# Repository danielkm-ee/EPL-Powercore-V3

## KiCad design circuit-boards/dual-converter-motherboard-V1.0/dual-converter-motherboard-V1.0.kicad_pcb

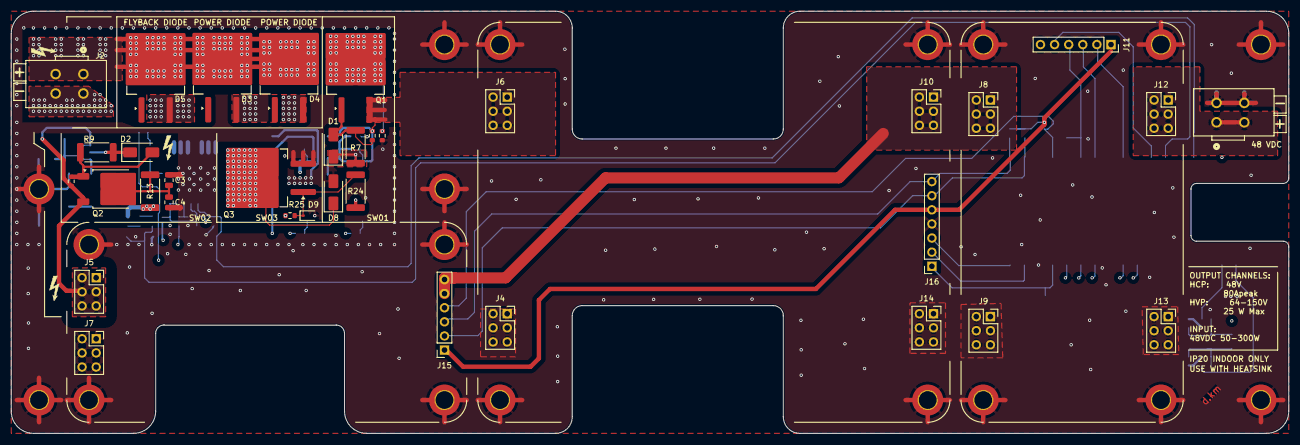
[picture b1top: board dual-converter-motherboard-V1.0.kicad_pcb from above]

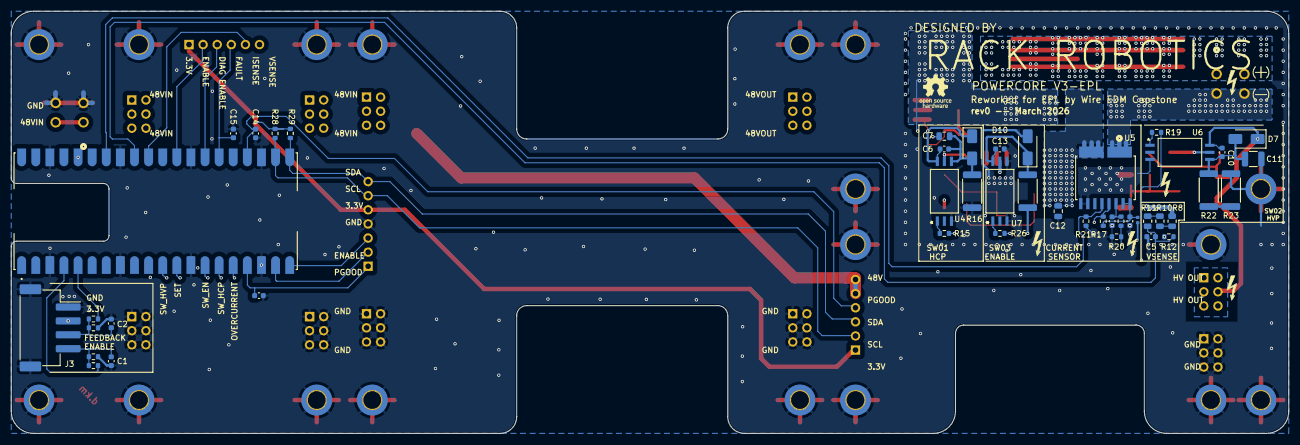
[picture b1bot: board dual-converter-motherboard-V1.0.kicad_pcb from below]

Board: 6 copper layers, 230.0 x 76.0 mm, 98 parts (45 on the bottom side), 49 nets.

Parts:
C1, C6, C8, C9, C10, C13: 220 nF; C_0603_1608Metric
C2, C14, C15, C16: 10000 pF; C_0603_1608Metric
C3, C4, C12: 10 nF; C_0805_2012Metric
C5: pF; C_0603_1608Metric
C7: 0.47 uF; C_0805_2012Metric
C11: 0.1 uF; C_1210_3225Metric
D1, D2, D8: US1M-13-F; D_SMA
D3, D4, D5: STPSC20065GY-TR
D6, D7, D10: D_Zener; D_SMA
D9: D_Zener; D_SOD-323
H1, H2, H3, H4, H5, H6, H7, H8, H9, H10, H11, H12, H13, H14, H15, H16, H17, H18: M3_DIN; MountingHole_3.2mm_M3_DIN965_Pad_TopBottom
J1, J2: 2601-1102
J3: S4B-XH-SM4-TB
J4, J5, J6, J7, J8, J9, J10, J12, J13, J14: Conn_02x03_Odd_Even; PinSocket_2x03_P2.54mm_Vertical
J11, J15: Conn_01x06_Socket; PinSocket_1x06_P2.54mm_Vertical
J16: Conn_01x07_Socket; PinSocket_1x07_P2.54mm_Vertical
L1: BBUP00100505330Y00; L_0402_1005Metric
Q1: SUM110P08-11L-E3
Q2: DMP45H4D9HK3-13
Q3: SIHB068N60EF-GE3; TO-263-2
R1, R2: 1K; R_0603_1608Metric
R3, R4, R12, R14, R17, R20, R21, R25: 10K; R_0603_1608Metric
R5, R6: 255K; R_0603_1608Metric
R7, R9, R24: 10R; R_2512_6332Metric
R8, R10, R11: 332K; R_0805_2012Metric
R13: 1R; R_2512_6332Metric
R15, R19, R26: 100R; R_0603_1608Metric
R16, R27: 1K; R_2512_6332Metric
R18, R28, R29: 2.2K; R_0603_1608Metric
R22, R23: 12K; R_2512_6332Metric
U4, U6, U7: UCC23313BDWYR
U5: TMCS1133C1A; TMCS1133C3AQDVGR
U8: SC0915

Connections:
+3.3V: J3.2, J11.1, J15.1, J16.5, L1.2, R28.2, R29.2, U8.36 (3V3_OUT)
+18V: C13.1, D10.1 (K), R27.1, U7.6 (VCC)
+48V: J8.1, J8.2, J8.3, J8.4, J8.5, J8.6, J10.1, J10.2, J10.3, J10.4, J10.5, J10.6, J15.5, J15.6, R27.2
/48VIN: J1.1 (1_1), J1.2 (1_2), J12.1, J12.2, J12.3, J12.4, J12.5, J12.6
/BOOST-CONVERTER-OUTPUT: C10.1, D7.1 (K), J5.1, J5.2, J5.3, J5.4, J5.5, J5.6, Q2.3 (S), R6.1, U6.6 (VCC)
/BOOST_PGOOD: C14.1, J15.4, U8.24 (GP18)
/BUCK-CONVERTER-OUTPUT: C6.1, D6.1 (K), J6.1, J6.2, J6.3, J6.4, J6.5, J6.6, Q1.3 (S), R5.1, U4.6 (VCC)
/BUCK_ADJ_PWM: J16.3, U8.20 (GP15)
/BUCK_ENABLE: J16.2, U8.19 (GP14)
/BUCK_POWER_GOOD: C16.1, J16.1, U8.17 (GP13)
/EDM_ELECTRODE(+): D3.1 (K), D4.1 (K), D5.1 (K), J2.1 (1_1), J2.2 (1_2), R8.1, R13.1
/EDM_ELECTRODE(-): D5.2 (A), J2.3 (2_1), J2.4 (2_2), U5.1 (IN+)
/I2C_SCL: J15.2, J16.6, R28.1, U8.22 (GP17)
/I2C_SDA: J15.3, J16.7, R29.1, U8.21 (GP16)
/PMM_DIAG_EN: J11.3, U8.27 (GP21)
/PMM_ENABLE: J11.2, U8.29 (GP22)
/PMM_FAULT: C15.1, J11.4, U8.26 (GP20)
/PMM_ISENSE: J11.5, U8.31 (GP26)
/controller/ADC1: C5.1, R11.2, R12.1, U8.32 (GP27)
/controller/ADC2: R21.1, U5.6 (VOUT), U8.34 (GP28)
/controller/EDM_ENABLE: R1.2, U8.4 (GP2)
/controller/EDM_FEEDBACK: R2.2, U8.5 (GP3)
/controller/OUTPUT_OVERCURRENT: R17.2, U5.7 (OC), U8.16 (GP12)
/controller/OUTPUT_OVERCURRENT_SET: R18.1, R20.1, U8.12 (GP9)
/controller/SW_ENABLE: R26.2, U8.14 (GP10)
/controller/SW_HIGH-CURRENT-PHASE: R15.2, U8.15 (GP11)
/controller/SW_HIGH-VOLTAGE-PHASE: R19.2, U8.11 (GP8)
/output-stage/SW01_GATE: D1.1 (K), R7.1, U4.5 (VOUT)
/output-stage/SW02_GATE: D2.1 (K), R9.1, U6.5 (VOUT)
/output-stage/SW03_GATE: R24.1, U7.5 (VOUT)
GND: C1.2, C2.2, C3.2, C4.2, C5.2, C7.2, C8.2, C9.2, C11.2, C12.2, C13.2, C14.2, C15.2, C16.2, D8.2 (A), D9.2 (A), D10.2 (A), H1.1, H2.1, H3.1, H4.1, H5.1, H6.1, H7.1, H8.1, H9.1, H10.1, H11.1, H12.1, H13.1, H14.1, H15.1, H16.1, H17.1, H18.1, J1.3 (2_1), J1.4 (2_2), J3.1, J3.MP, J4.1, J4.2, J4.3, J4.4, J4.5, J4.6, J7.1, J7.2, J7.3, J7.4, J7.5, J7.6, J9.1, J9.2, J9.3, J9.4, J9.5, J9.6, J13.1, J13.2, J13.3, J13.4, J13.5, J13.6, J14.1, J14.2, J14.3, J14.4, J14.5, J14.6, J16.4, Q3.3 (S), R3.2, R4.2, R12.2, R14.2, R16.1, R20.2, R21.2, R23.2, R25.2, U4.3 (CATHODE), U5.3 (GND), U5.4 (ALERT), U6.3 (CATHODE), U7.3 (CATHODE), U7.4 (VEE), U8.3 (GND), U8.8 (GND__1), U8.13 (GND__2), U8.18 (GND__3), U8.23 (GND__4), U8.28 (GND__5), U8.33 (AGND), U8.38 (GND__6)
unnamed: C8.1, L1.1, R17.1, U5.9 (VS), U5.10 (VS)
unnamed: D1.2 (A), Q1.2 (G), R5.2, R7.2
unnamed: D2.2 (A), Q2.2 (G), R6.2, R9.2
unnamed: D3.2 (A), D4.2 (A), Q1.1 (D), R14.1
unnamed: C6.2, C7.1, D6.2 (A), R16.2, U4.4 (VEE)
unnamed: C10.2, C11.1, D7.2 (A), R22.1, U6.4 (VEE)
unnamed: C12.1, D8.1 (K), Q3.2 (D), U5.2 (IN-)
unnamed: D9.1 (K), Q3.1 (G), R24.2, R25.1
unnamed: C2.1, J3.3, R2.1, R4.1
unnamed: C1.1, J3.4, R1.1, R3.1
unnamed: C3.1, C4.1, Q2.1 (D), R13.2
unnamed: R8.2, R10.1
unnamed: R10.2, R11.1
unnamed: R22.2, R23.1
unnamed: R15.1, U4.1 (ANODE)
unnamed: C9.1, R18.2, U5.8 (VOC)
unnamed: R19.1, U6.1 (ANODE)
unnamed: R26.1, U7.1 (ANODE)

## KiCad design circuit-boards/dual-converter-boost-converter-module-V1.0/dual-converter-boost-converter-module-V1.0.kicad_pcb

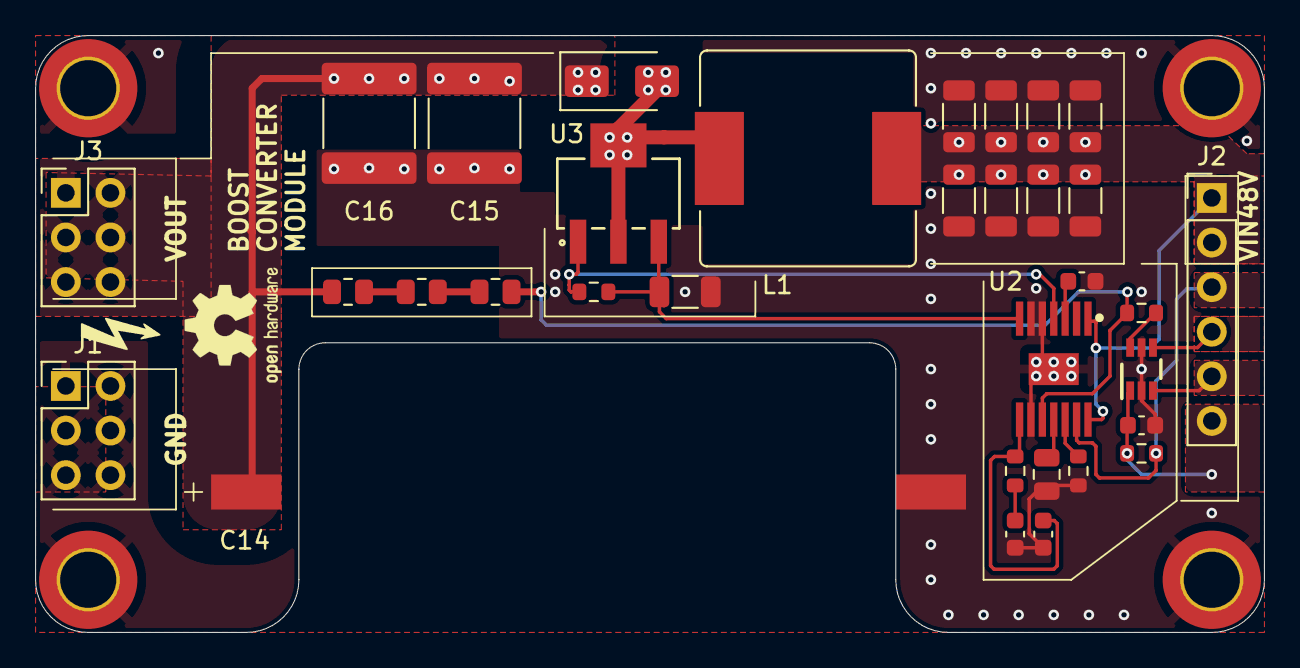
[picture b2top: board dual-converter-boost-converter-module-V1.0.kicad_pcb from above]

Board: 4 copper layers, 70.0 x 34.0 mm, 37 parts (0 on the bottom side), 19 nets.

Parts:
C1, C2, C3, C4, C6, C7, C8, C9: 10 uF; C_1206_3216Metric
C5, C10: 1 uF; C_0603_1608Metric
C11: 33 uF; C_0805_2012Metric
C12: 39nF; C_0603_1608Metric
C13: F; C_0603_1608Metric
C14: 22UF; 226TTA350M
C15, C16: 2.2 uF; C_2220_5750Metric
D1: US1M-13-F; D_SMA
H1, H2, H3, H4: M3_DIN; MountingHole_3.2mm_M3_DIN965_Pad_TopBottom
J1, J3: Vout Conn; PinHeader_2x03_P2.54mm_Vertical
J2: Conn_01x06; PinHeader_1x06_P2.54mm_Vertical
L1: 680 uH; SRR1210-681M
R1, R2, R3: 200K; R_0805_2012Metric
R4, R5: 2.2K; R_0603_1608Metric
R6: 49.3K; R_0603_1608Metric
R7: 15K; R_0603_1608Metric
R8: 100K; R_0603_1608Metric
R9: 90mR; R_1206_3216Metric
U1: TPL0401B-10DCKR
U2: LM5156HPWPR; lm5156h
U3: STN3N40K3

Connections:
+3.3V: C5.1, J2.6, R5.1, U1.1 (VDD)
+48V: C1.1, C2.1, C3.1, C4.1, C6.1, C7.1, C8.1, C9.1, J2.1, J2.2, L1.1, U2.1 (BIAS), U2.14 (EN_UVLO_SYNC)
/BOOST_PGOOD: J2.3, R5.2, U2.13 (PGOOD)
/BOOST_SWITCH_NET: D1.2 (A), L1.2, U3.2 (D), U3.4 (D)
/COMPENSATION: C13.1, R7.1, U2.8 (COMP)
/COUT_BOOST: C14.1, C15.1, C16.1, D1.1 (K), J3.1, J3.2, J3.3, J3.4, J3.5, J3.6, R1.1
/CURRENT_SENSE: R8.2, R9.1, U2.7 (CS), U3.3 (S)
/GATE_NET: R8.1, U2.4 (GATE), U3.1 (G)
/V_FEEDBACK: R3.2, R4.2, U2.10 (FB)
GND: C1.2, C2.2, C3.2, C4.2, C5.2, C6.2, C7.2, C8.2, C9.2, C10.2, C11.2, C12.2, C13.2, C14.2, C15.2, C16.2, H1.1, H2.1, H3.1, H4.1, J1.1, J1.2, J1.3, J1.4, J1.5, J1.6, R6.2, R9.2, U1.2 (GND), U1.5 (W), U2.5 (PGND), U2.6 (AGND), U2.9 (DITHOFF), U2.15 (EP)
unnamed: C12.1, R7.2
unnamed: J2.4, U1.4 (SDA)
unnamed: J2.5, U1.3 (SCL)
unnamed: R1.2, R2.1
unnamed: R2.2, R3.1
unnamed: R4.1, U1.6 (H)
unnamed: R6.1, U2.12 (RT)
unnamed: C11.1, U2.11 (SS)
unnamed: C10.1, U2.3 (VCC)

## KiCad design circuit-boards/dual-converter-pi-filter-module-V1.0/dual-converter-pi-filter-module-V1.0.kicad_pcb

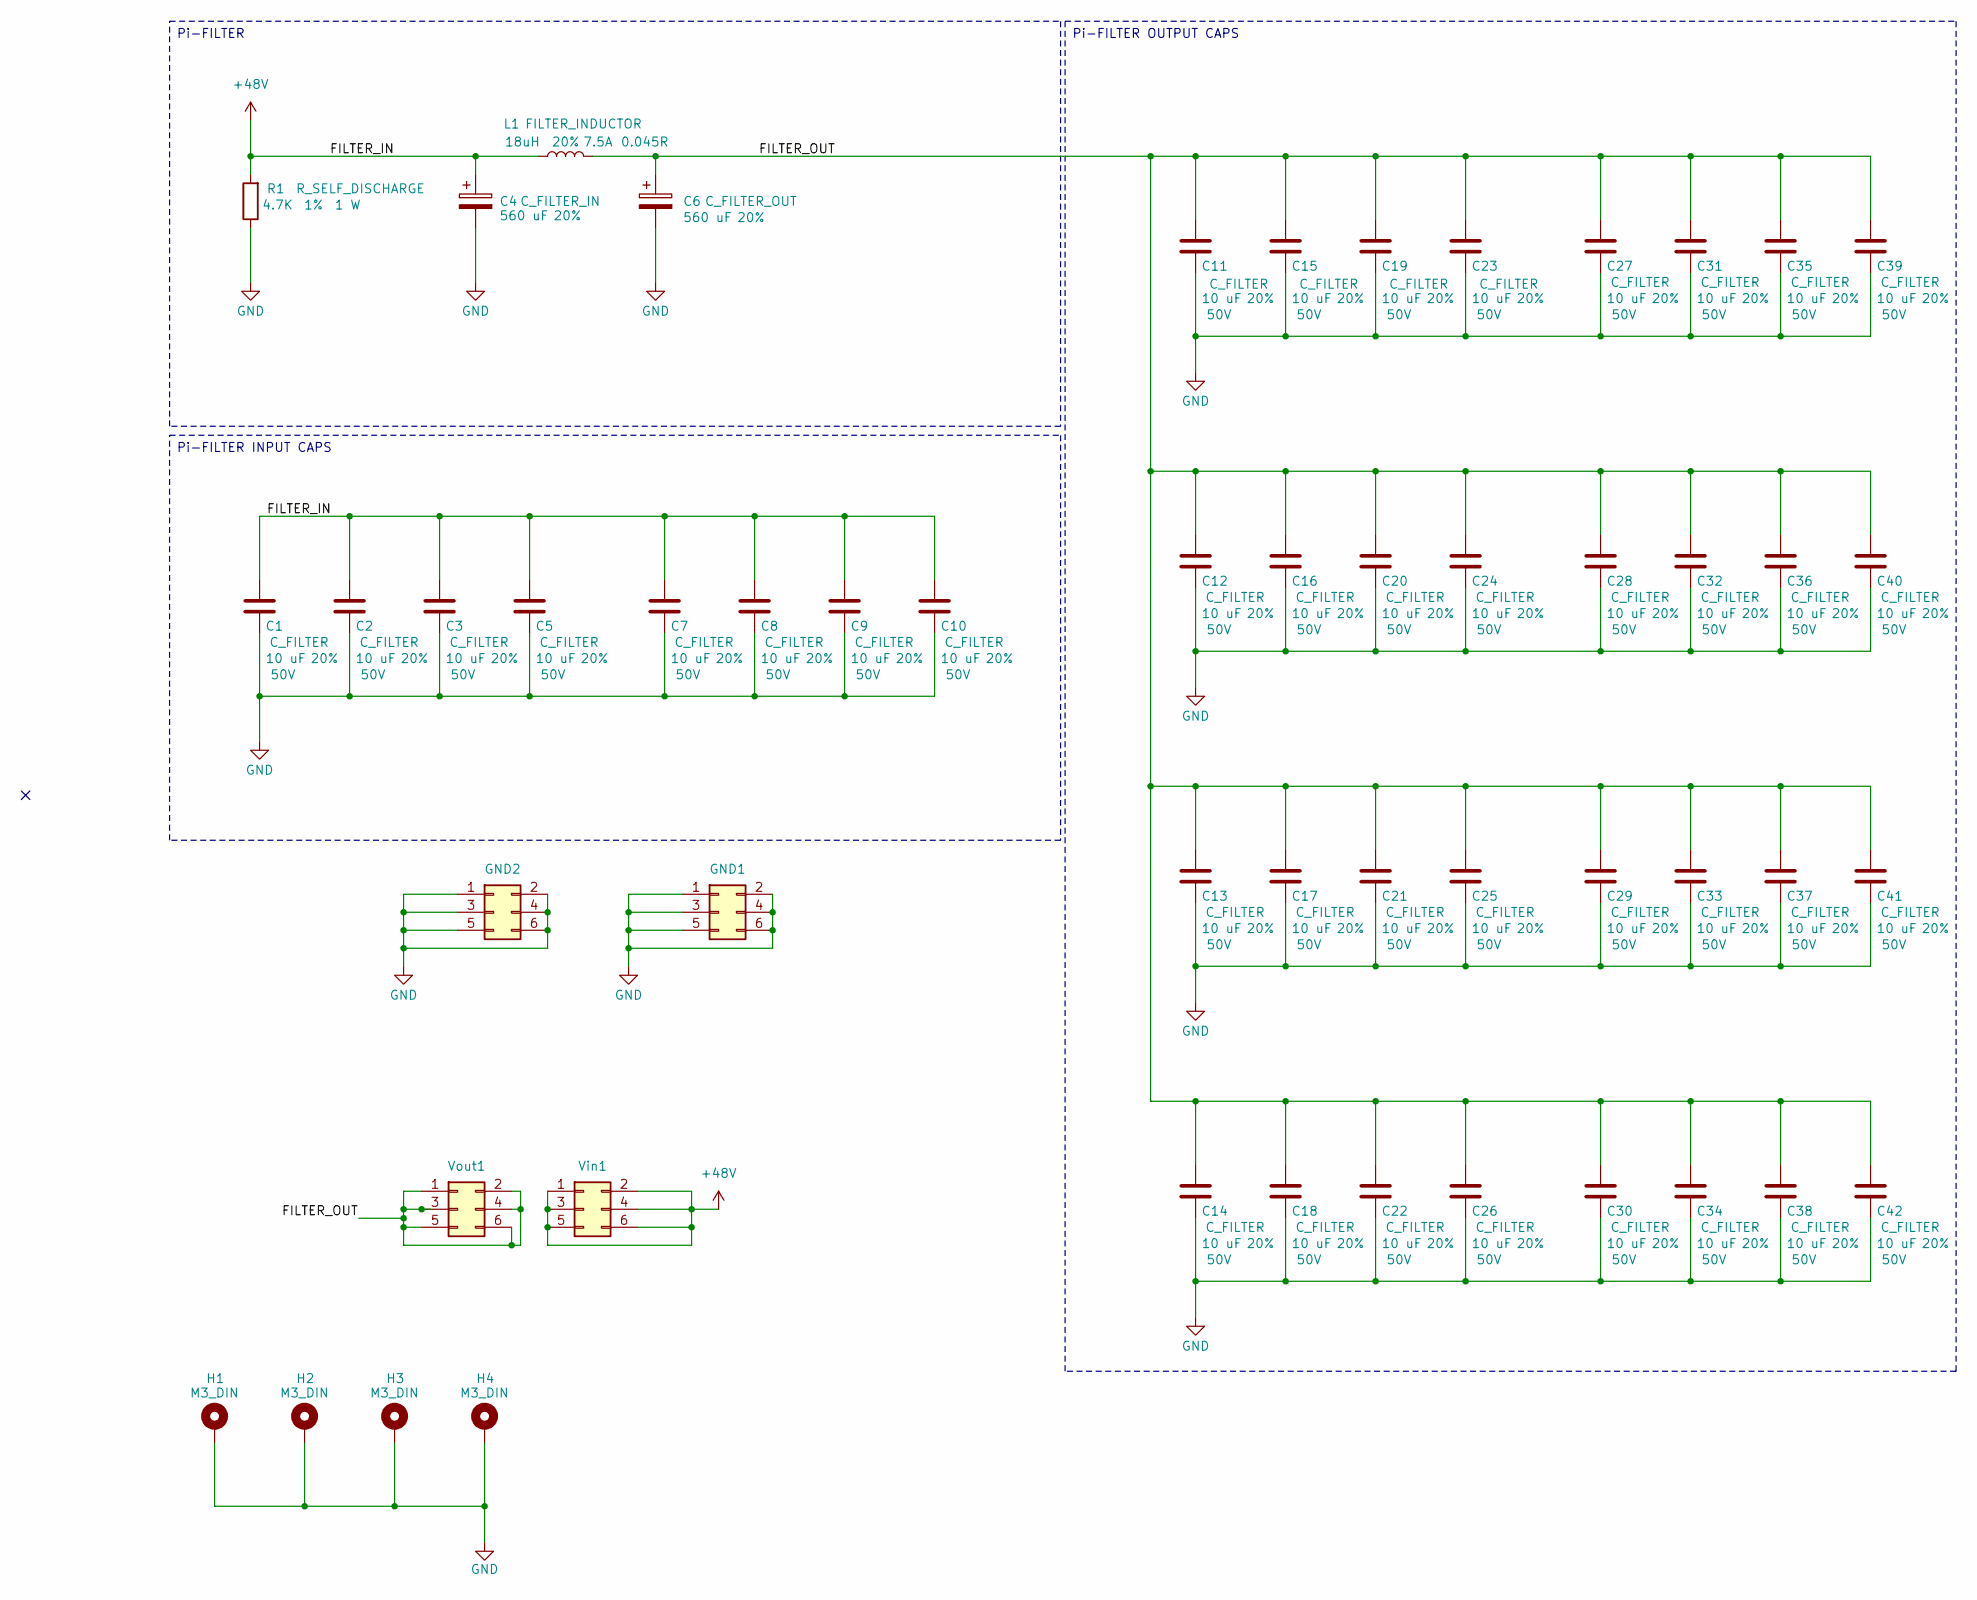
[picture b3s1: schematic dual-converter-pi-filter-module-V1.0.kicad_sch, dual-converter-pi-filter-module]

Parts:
C1, C2, C3, C5, C7, C8, C9, C10, C11, C12, C13, C14, C15, C16, C17, C18, C19, C20, C21, C22, C23, C24, C25, C26, C27, C28, C29, C30, C31, C32, C33, C34, C35, C36, C37, C38, C39, C40, C41, C42: 10 uF; C_1206_3216Metric; Tolerance 20%; Max Voltage 50V; Manufacturer# CL31A106MBHNNNE; LCSC Part # C96600
C4, C6: 560 uF; PHA225; Tolerance 20%; Manufacturer# PHA225MLP3560QE4; LCSC Part # C3274794
GND1, GND2: Conn_02x03_Odd_Even; PinHeader_2x03_P2.54mm_Vertical
H1, H2, H3, H4: M3_DIN; MountingHole_3.2mm_M3_DIN965_Pad_TopBottom; Manufacturer# NULL
L1: 18uH; SRP1245A; Tolerance 20%; Current Rating 7.5A; Manufacturer# SRP1245A-180M; LCSC Part # C5926042
R1: 4.7K; R_2512_6332Metric; Tolerance 1%; Manufacturer# RC2512JK-074K7L; LCSC Part # C878291
Vin1: Conn_02x03_Odd_Even; PinHeader_2x03_P2.54mm_Vertical
Vout1: Conn_02x03_Odd_Even; PinHeader_2x03_P2.54mm_Vertical

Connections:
+48V: C1.1, C2.1, C3.1, C4.1, C5.1, C7.1, C8.1, C9.1, C10.1, L1.1, R1.2, Vin1.1, Vin1.2, Vin1.3, Vin1.4, Vin1.5, Vin1.6
/FILTER_OUT: C6.1, C11.1, C12.1, C13.1, C14.1, C15.1, C16.1, C17.1, C18.1, C19.1, C20.1, C21.1, C22.1, C23.1, C24.1, C25.1, C26.1, C27.1, C28.1, C29.1, C30.1, C31.1, C32.1, C33.1, C34.1, C35.1, C36.1, C37.1, C38.1, C39.1, C40.1, C41.1, C42.1, L1.2, Vout1.1, Vout1.2, Vout1.3, Vout1.4, Vout1.5, Vout1.6
GND: C1.2, C2.2, C3.2, C4.2, C5.2, C6.2, C7.2, C8.2, C9.2, C10.2, C11.2, C12.2, C13.2, C14.2, C15.2, C16.2, C17.2, C18.2, C19.2, C20.2, C21.2, C22.2, C23.2, C24.2, C25.2, C26.2, C27.2, C28.2, C29.2, C30.2, C31.2, C32.2, C33.2, C34.2, C35.2, C36.2, C37.2, C38.2, C39.2, C40.2, C41.2, C42.2, GND1.1, GND1.2, GND1.3, GND1.4, GND1.5, GND1.6, GND2.1, GND2.2, GND2.3, GND2.4, GND2.5, GND2.6, H1.1, H2.1, H3.1, H4.1, R1.1

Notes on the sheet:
Pi-FILTER INPUT CAPS
Pi-FILTER
Pi-FILTER OUTPUT CAPS

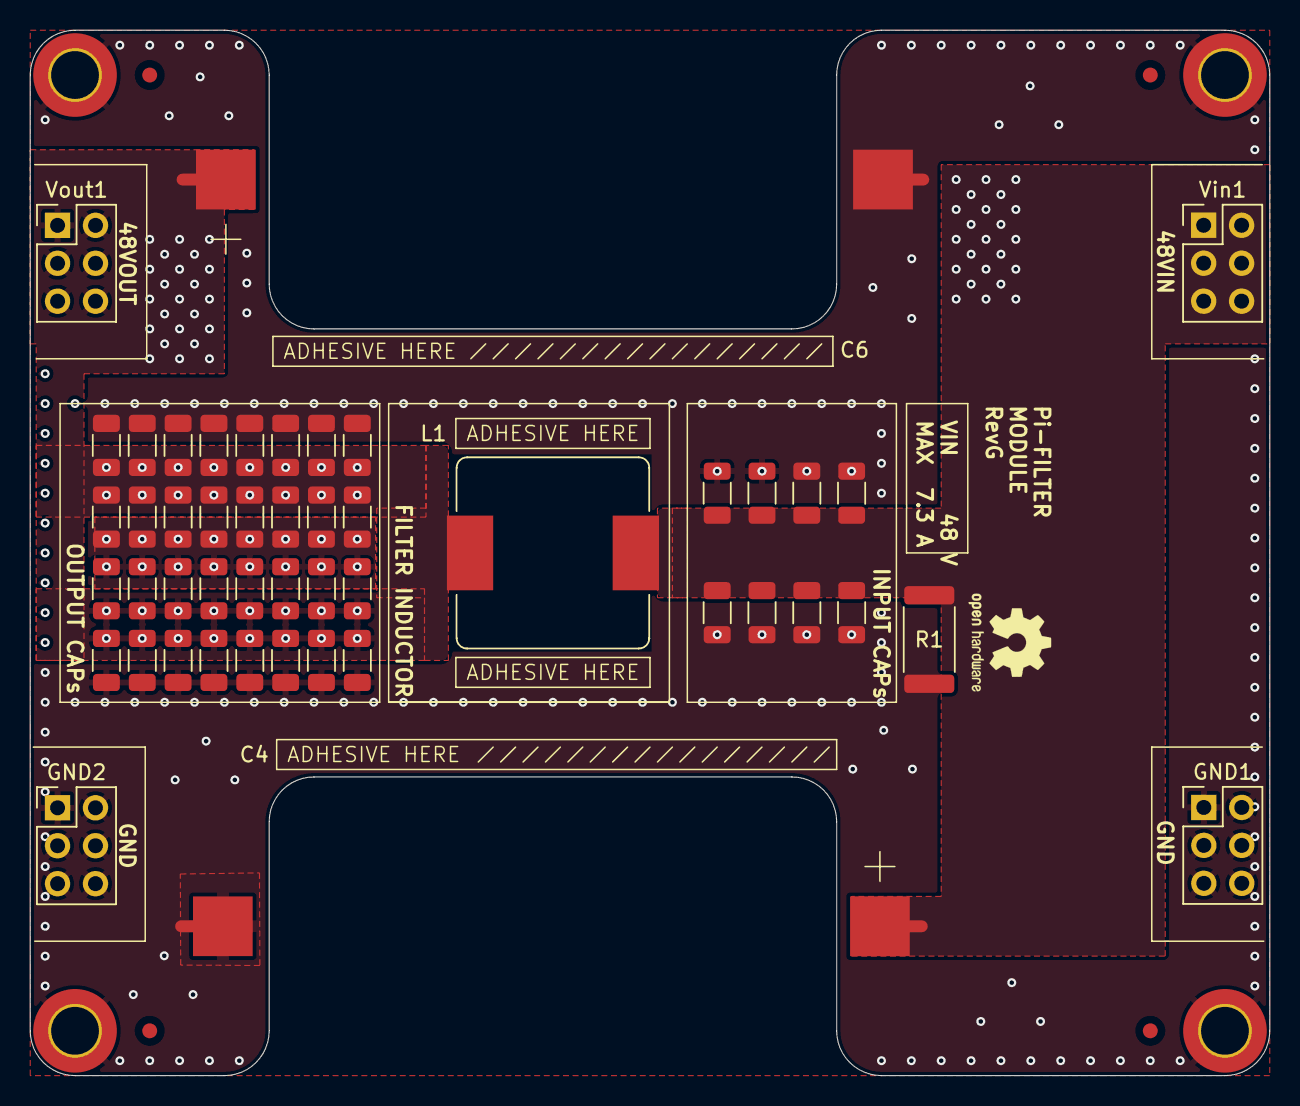
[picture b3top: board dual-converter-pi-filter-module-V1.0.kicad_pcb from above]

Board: 4 copper layers, 83.0 x 70.0 mm, 52 parts (0 on the bottom side), 3 nets.

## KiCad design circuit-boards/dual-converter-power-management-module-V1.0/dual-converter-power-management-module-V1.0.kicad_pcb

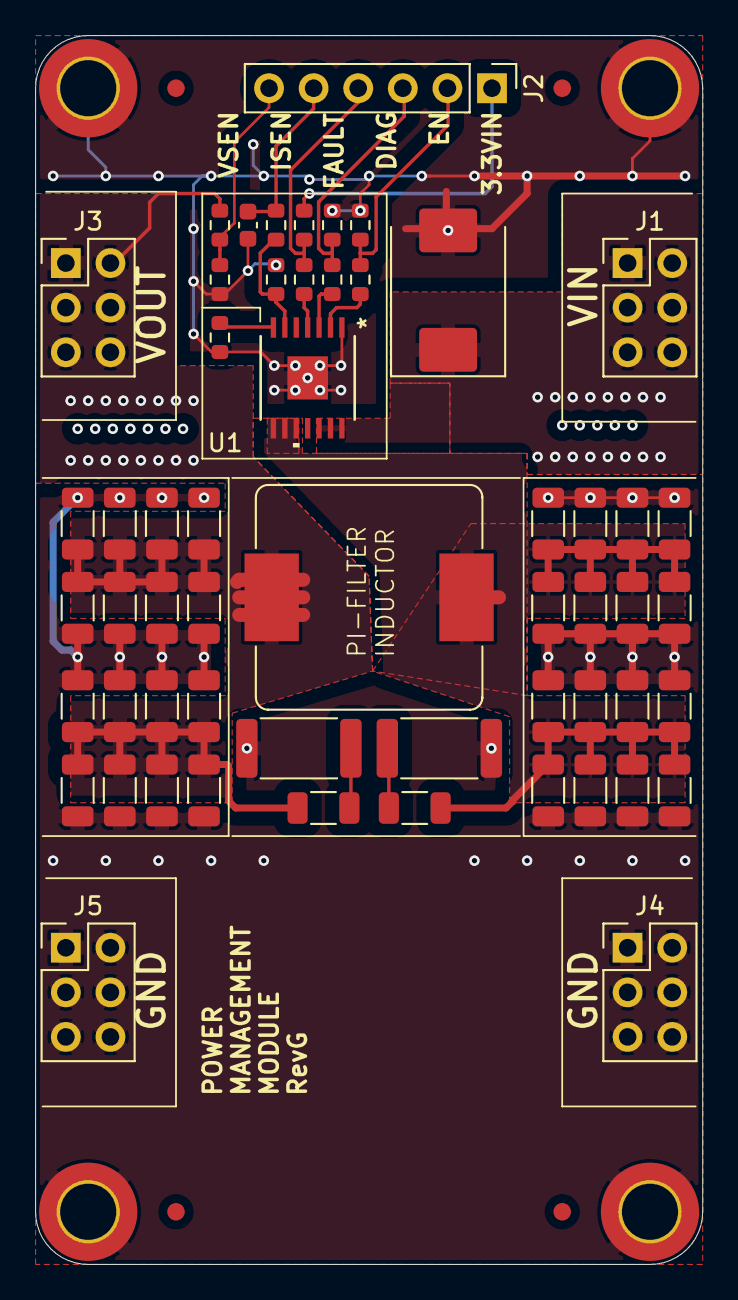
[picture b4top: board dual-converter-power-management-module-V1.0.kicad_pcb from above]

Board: 4 copper layers, 38.0 x 70.0 mm, 60 parts (0 on the bottom side), 17 nets.

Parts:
C1: 1 uF; C_0603_1608Metric
C2, C3, C4, C5, C6, C7, C8, C9, C10, C11, C12, C13, C14, C15, C16, C17, C18, C19, C20, C21, C22, C23, C24, C25, C26, C27, C28, C29, C30, C31, C32, C33, C34, C35: 10 uF; C_1206_3216Metric
D1: SMCJ60A-E3/57T; D_SMC
H1, H2, H3, H4: M3_DIN; MountingHole_3.2mm_M3_DIN965_Pad_TopBottom
J1, J3, J4, J5: Conn_02x03_Odd_Even; PinHeader_2x03_P2.54mm_Vertical
J2: Conn_01x06_Pin; PinHeader_1x06_P2.54mm_Vertical
L1: 18uH; SRP1245A
R1, R6, R7: 100K; R_0603_1608Metric
R2, R3, R4, R5: 2.2K; R_0603_1608Metric
R8: 249R; R_0603_1608Metric
R9: 0R; R_0603_1608Metric
R10, R13: 1R; R_2512_6332Metric
R11: 172K; R_0603_1608Metric
R12: 10K; R_0603_1608Metric
U1: TPS1HTC30AQPWPRQ1; TPS1HTC30-Q1

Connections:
+3.3V: J2.1, R1.1
+48V: C19.1, C20.1, C21.1, C22.1, C23.1, C24.1, C25.1, C26.1, C27.1, C28.1, C29.1, C30.1, C31.1, C32.1, C33.1, C34.1, C35.1, J3.1, J3.2, J3.3, J3.4, J3.5, J3.6, L1.2, R11.1
+48VIN: D1.1 (A1), J1.1, J1.2, J1.3, J1.4, J1.5, J1.6, U1.12 (VS), U1.13 (VS), U1.14 (VS)
/FILTER_IN: C2.1, C3.1, C4.1, C5.1, C6.1, C7.1, C8.1, C9.1, C10.1, C11.1, C12.1, C13.1, C14.1, C15.1, C16.1, C17.1, C18.1, L1.1, U1.8 (VOUT), U1.9 (VOUT), U1.10 (VOUT)
GND: C1.2, C2.2, C3.2, C4.2, C5.2, C6.2, C7.2, C8.2, C9.2, C11.2, C12.2, C13.2, C14.2, C15.2, C16.2, C17.2, C18.2, C19.2, C20.2, C21.2, C22.2, C23.2, C24.2, C25.2, C26.2, C28.2, C29.2, C30.2, C31.2, C32.2, C33.2, C34.2, C35.2, D1.2 (A2), H1.1, H2.1, H3.1, H4.1, J4.1, J4.2, J4.3, J4.4, J4.5, J4.6, J5.1, J5.2, J5.3, J5.4, J5.5, J5.6, R6.2, R7.2, R8.2, R9.2, R10.2, R12.2, R13.2, U1.1 (GND)
unnamed: C10.2, R10.1
unnamed: C27.2, R13.1
unnamed: J2.2, R2.1, R6.1
unnamed: J2.3, R3.1, R7.1
unnamed: J2.4, R1.2, R4.1
unnamed: C1.1, J2.5, R5.1
unnamed: R4.2, U1.4 (*FAULT)
unnamed: R3.2, U1.3 (DIAG_EN)
unnamed: R2.2, U1.2 (EN)
unnamed: R9.1, U1.7 (ILIM)
unnamed: R5.2, R8.1, U1.6 (SNS)
VSense: J2.6, R11.2, R12.1

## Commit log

2025-09-24 RevH Motherboard
    - removed unused vias from HVP switch
    = removed unused fiducials
    - silkscreen minor fixes to labels
2025-09-30 Added CAD to Powercore V3
    Upon request from customers
2026-02-14 replaced thermal reliefs with solid fills on high power traces
2026-02-18 begin replacing pogo pins with pin headers. todo: fix ugly schematic, add non power connections
2026-02-22 Replaced Pogo pins for pin headers, zone changes, deletion of vias and pads
2026-02-22 Replaced pogo pins with pin headers
2026-02-22 Deleted castellated edges and put in 2 by 3 pin header connectors, made all fillings solid
2026-02-23 add connectors for non-power pins, improve schematic readability
2026-02-23 add signal connector sockets, fix routing, rough-out locations
2026-02-23 fix corrupted pcb after merge issues
2026-02-24 align and lock connectors and mountpoints. improve track sizing and layout
2026-02-24 motherboard: align and lock connectors and mountpoints, add cutout for pico test points, fix pico footprint, improve tracks
2026-02-24 powerman: align and lock connectors and mountpoints, increase clearance and spacing on high voltage traces
2026-02-24 pifilter: align and lock connectors and mountpoints
2026-02-24 final drc checks, silkscreen edits, added stitching vias to motherboard and pi filter
2026-02-25 fix edgecut interference with trace
